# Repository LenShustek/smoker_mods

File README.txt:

This is a repository that documents my modifications to the 
Masterbuilt MES130B food smoker. 

It's a serviceable appliance, and we've made some great meals with it, 
but it suffers from a number of defects. You can read my posting to 
www.smokingmeatforums.com about them in the file forum_posting.txt. 

The first modification I made is to keep the smoke production going 
when the main (and only) heating element turns off to allow the 
temperature to come down. I put some heating elements in the bottom of 
the wood chip tray, and turn them on periodically whenever the main 
heater is off. 

The details are in the chipheater directory. There are two 100W heating 
elements wired in series, so 50W power dissipation. To control them I 
tapped into the 4-wire cable (ground, 5VDC power, heater on, and 
temperature sense) that goes to Masterbuilt's controller, and connected 
a little circuit that switches a small solid-state relay. A knob adjusts 
the duty cycle: it's on for 10 seconds and off for 2 to 18 seconds. It 
seems to be working fine. 

The second modification was to replace the Masterbuilt controller with
one based on an inexpensive PID (proportional-integral-differential) 
controller, interfaced to the smoker with a small circuit. This keeps
the temperature at the set point within a degree or two, rather than
having huge overshoot and undershoot by 10-15 degrees in each direction, 
with a cycle time of about 15 minutes. 

The details are in the PID_interface directory. In particular, see
the PID_addition_instructions file for instructions and photos.
This modification doesn't require the smoker unit itself to be
taken apart, or any of its 120V AC wiring changed.

Len Shustek 13 November 2020 
updated 29 November 2020

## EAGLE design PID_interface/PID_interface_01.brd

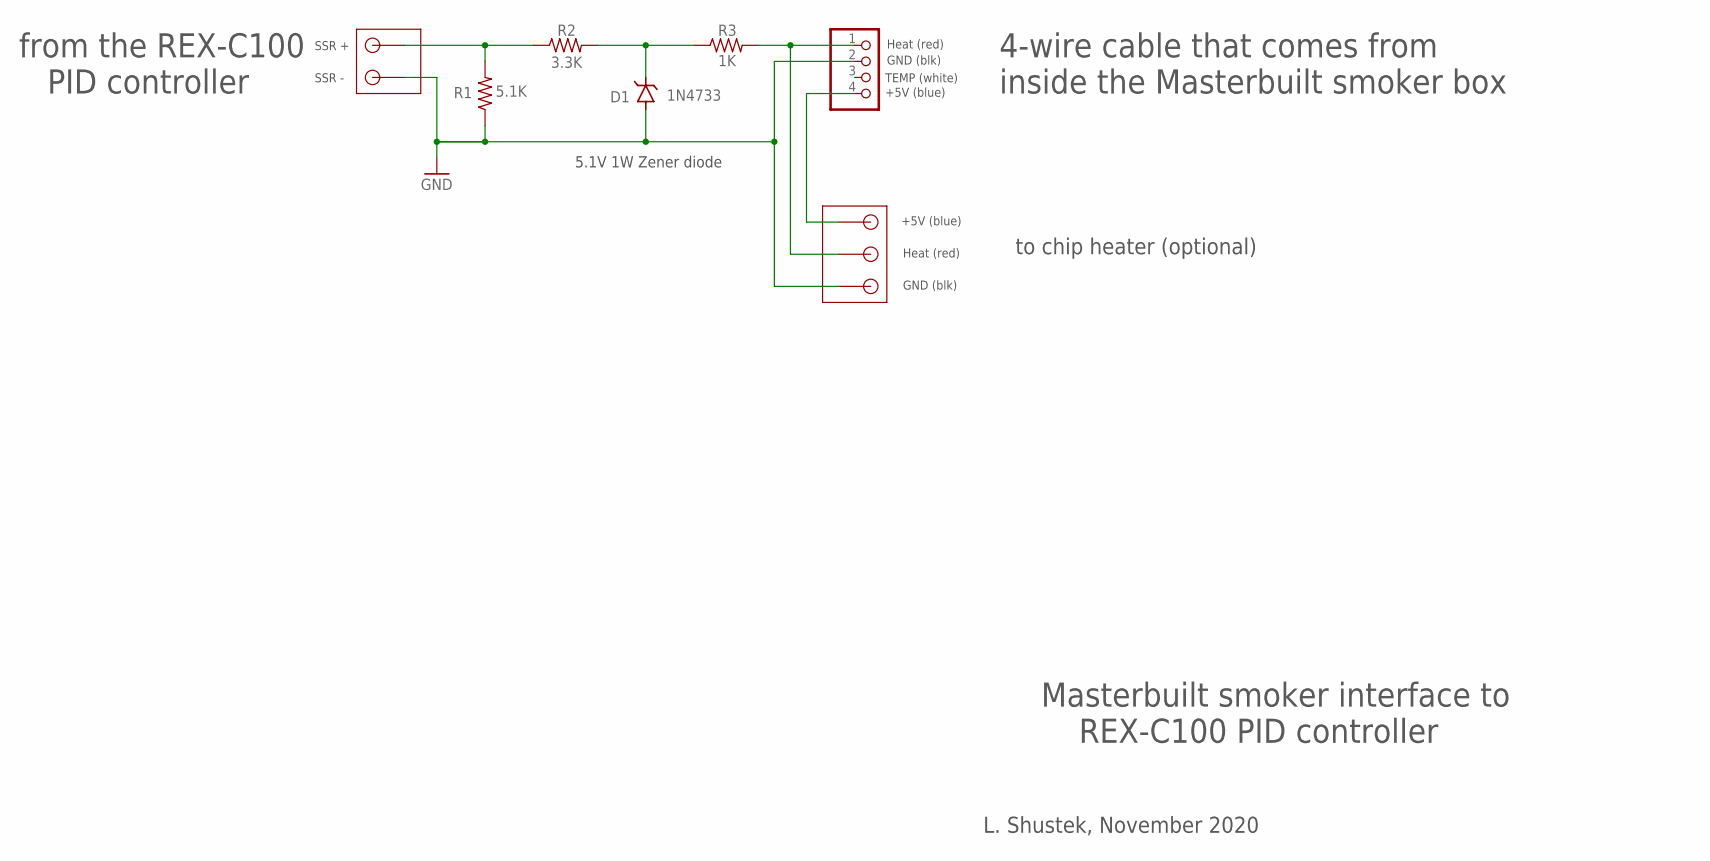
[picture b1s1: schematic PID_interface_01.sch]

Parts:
D1: 1N4733; DO35-10
JP1: PINHD-1X4; 1X04
R1: 5.1K; 0207/10
R2: 3.3K; 0207/10
R3: 1K; 0207/10
U$1: CONNECTOR-2PINTHIN; CONNECTOR-2PIN-5MM_THIN
U$2: CONNECTOR-3PIN; CONNECTOR-3PIN-5MM_THIN

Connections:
+5V: JP1.4, U$2.P$1
GND: D1.A, JP1.2, R1.1, U$1.P$1, U$2.P$3
HEAT: JP1.1, R3.2, U$2.P$2
unnamed: R1.2, R2.1, U$1.P$2
unnamed: D1.C, R2.2, R3.1

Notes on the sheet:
Masterbuilt smoker interface to REX-C100 PID controller
L. Shustek, November 2020
Heat (red)
GND (blk)
TEMP (white)
+5V (blue)
4-wire cable that comes from inside the Masterbuilt smoker box
SSR -
SSR +
from the REX-C100 PID controller
5.1V 1W Zener diode
to chip heater (optional)

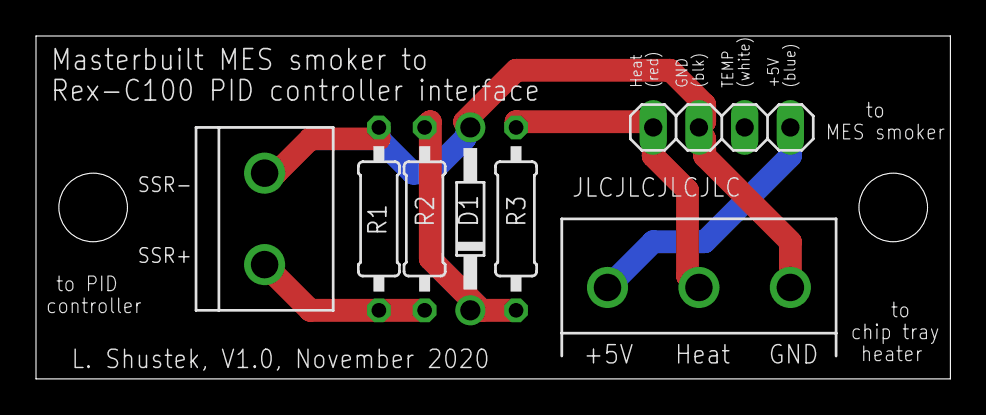
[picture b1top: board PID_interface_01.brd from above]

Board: 2 copper layers, 50.8 x 19.1 mm, 7 parts (0 on the bottom side), 5 nets.

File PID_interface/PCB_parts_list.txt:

Masterbuilt MES 130B to REX-C100 PID controller interface 
printed circuit board parts list

R1: 5.1K ohm 1/4 watt resistor
R2: 3.3K ohm 1/4 watt resistor
R3: 1K ohm 1/4 watt resistor
D1: 1N4733 5.1 volt 1 watt zener diode
4-pin single-row 0.1" spacing pin header
2-pin 0.2" spacing PCB mount screw terminal connector
3-pin 0.2" spacing PCB mount screw terminal connector (only needed for chip heater)

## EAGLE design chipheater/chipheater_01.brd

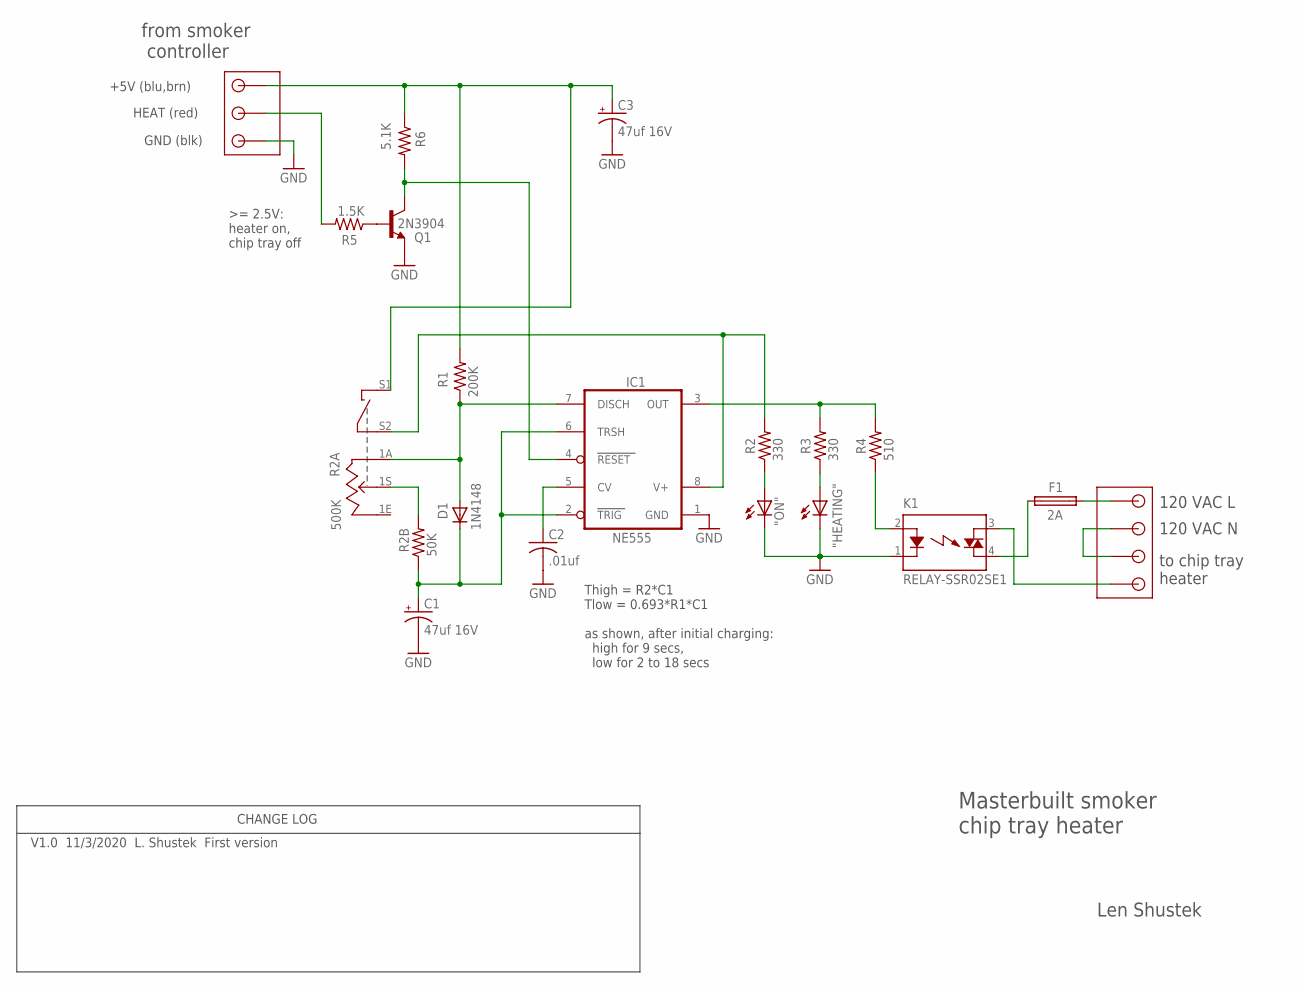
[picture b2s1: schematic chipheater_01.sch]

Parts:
"HEATING": LED5MM
"ON": LED5MM
C1, C3: 47uf 16V; E2,5-5
C2: .01uf; C025-025X050
D1: 1N4148; DO-1N4148
F1: 2A; SH22,5A
IC1: NE555; DIL08
K1: RELAY-SSR02SE1; RELAY-SSR
Q1: 2N3904; TO92
R1: 200K; 0204/7
R2, R3: 330; 0204/7
R2A: 500K; POT_W/SWITCH-UXCELL
R2B: 50K; 0204/7
R4: 510; 0204/7
R5: 1.5K; 0204/7
R6: 5.1K; 0204/7
U$1: CONNECTOR-4PIN; CONNECTOR-4PIN-5MM_THIN
U$2: CONNECTOR-3PIN; CONNECTOR-3PIN-5MM_THIN

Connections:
-RESET: IC1.4 (RESET), Q1.1 (C), R6.2
AC-L: F1.2, U$1.P$1
AC-N: U$1.P$2, U$1.P$3
GND: "HEATING".K (C), "ON".K (C), C1.-, C2.2, C3.-, IC1.1 (GND), K1.1 (K), Q1.3 (E), U$2.P$1
HEAT: R5.2, U$2.P$2
HTR: K1.3 (DS1), U$1.P$4
unnamed: "ON".A, R2.1
unnamed: Q1.2 (B), R5.1
unnamed: F1.1, K1.4 (DS2)
unnamed: IC1.8 (V+), R2.2, R2A.S2
unnamed: K1.2 (A), R4.1
unnamed: D1.A, IC1.7 (DISCH), R1.1, R2A.1A
unnamed: R2A.1S, R2B.2
unnamed: C2.1, IC1.5 (CV)
unnamed: C1.+, D1.C, IC1.2 (TRIG), IC1.6 (TRSH), R2B.1
unnamed: IC1.3 (OUT), R3.2, R4.2
unnamed: "HEATING".A, R3.1
VCC: C3.+, R1.2, R2A.S1, R6.1, U$2.P$3

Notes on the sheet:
Masterbuilt smoker chip tray heater
Len Shustek
V1.0 11/3/2020 L. Shustek First version
CHANGE LOG
120 VAC L
120 VAC N
to chip tray heater
+5V (blu,brn)
GND (blk)
HEAT (red)
from smoker controller
Thigh = R2*C1 Tlow = 0.693*R1*C1 as shown, after initial charging: high for 9 secs, low for 2 to 18 secs

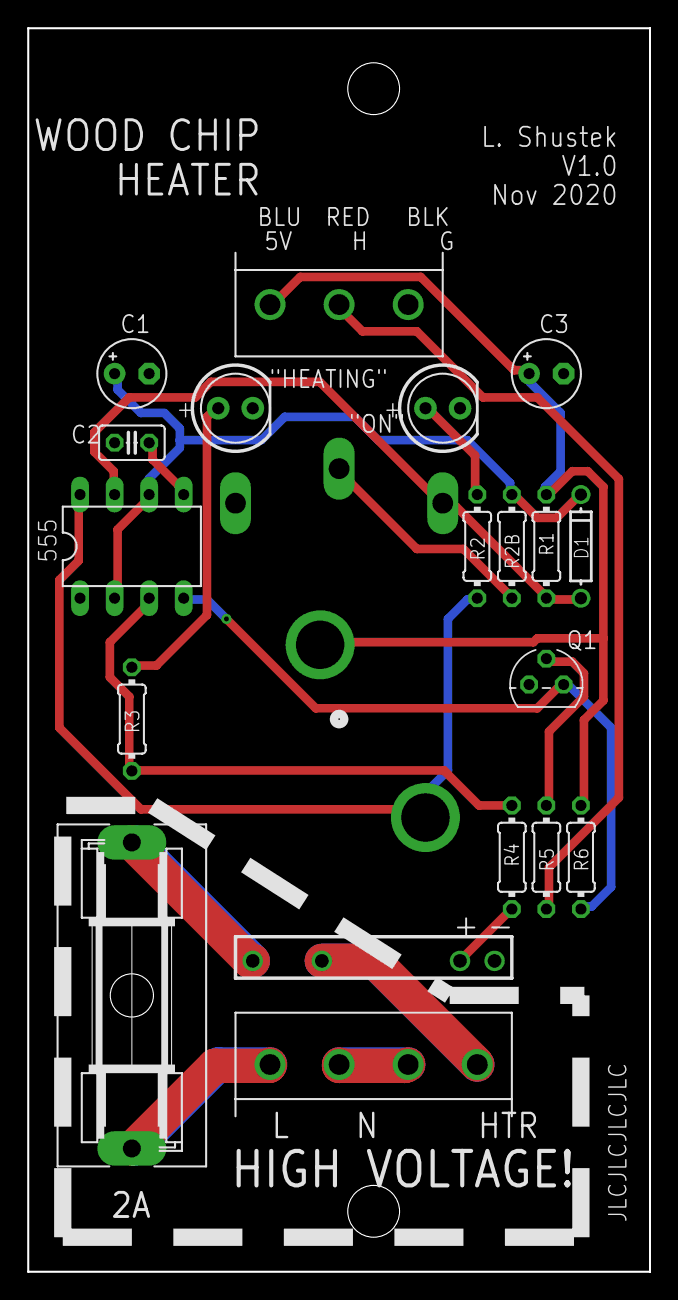
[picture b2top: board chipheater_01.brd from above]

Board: 2 copper layers, 45.7 x 91.4 mm, 20 parts (1 on the bottom side), 18 nets.

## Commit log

2020-11-13 Initial posting
2020-11-13 reformat
2020-11-30 PID controller mod
